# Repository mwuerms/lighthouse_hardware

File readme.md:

# Lighthouse - Hardware

## basic concept

+ lighthouse
+ buoy: hand sender, ble advertising

## lighthouse - electronics

### main board

- RF-MCU: nRF52840: [NINA-B302-00B Module](https://www.mouser.ch/ProductDetail/377-NINA-B302-00B) (ublox)
  - SWDIO connector (50 mil header)
  - RTC (optional): i2c + backup battery CV
  - sound module: [DFPlayer mini](https://wiki.dfrobot.com/DFPlayer_Mini_SKU_DFR0299)
  - display 1: display time
  - display 2: lighting, simulate sunrise
  - Buttons
  - Sensors
    - ambient light sensor (ALS)
      - [VEML7700-TR](https://www.mouser.ch/ProductDetail/78-VEML7700-TR)
      - [TMD37253M](https://www.mouser.ch/ProductDetail/985-TMD37253M) much more than ALS, also proximity and color sensor
      - also maybe [VEML3235](https://www.mouser.ch/ProductDetail/78-VEML3235), [VEML6035](https://www.mouser.ch/ProductDetail/78-VEML6035)
    - rh sensor
      - [SHT40-AD1B-R2](https://www.mouser.ch/ProductDetail/403-SHT40-AD1B-R2)
    - p sensor
      - [DPS368XTSA1](https://www.mouser.ch/ProductDetail/726-DPS368XTSA1)
    - microphone, maybe implement a "do I snore" functionality
      - [CMM-4030DT-26354-TR](https://www.mouser.ch/ProductDetail/490-CMM4030DT26354TR)

### display

- addressable LEDs: [IN-PI22TAT5R5G5B](https://www.mouser.ch/ProductDetail/743-IN-PI22TAT5R5G5B)

### buoy - electronics

- RF-MCU: nRF52811 module [ISP1907-LL-RS](https://www.mouser.ch/ProductDetail/359-ISP1907-LL-RS)
- battery CR2032
- vibration sensor [Adafruit 2384](https://www.mouser.ch/ProductDetail/485-2384)
- button PTS526 [PTS526 SK15 SMTR2 LFS](https://www.mouser.ch/ProductDetail/611-PTS526SK15SMR2L)
- SWDIO connector (50 mil header)

#### schematics

buoy will be soldered together using wire only, no pcb for this.

# links

just a collection of (maybe) useful links

- [markdown cheat sheet](https://www.markdownguide.org/cheat-sheet/)

# ideas

- add many sensors like
  - microphone, analyze snoring
- add memory/flash to log
  - sensor values
  - events
  - errors, ...

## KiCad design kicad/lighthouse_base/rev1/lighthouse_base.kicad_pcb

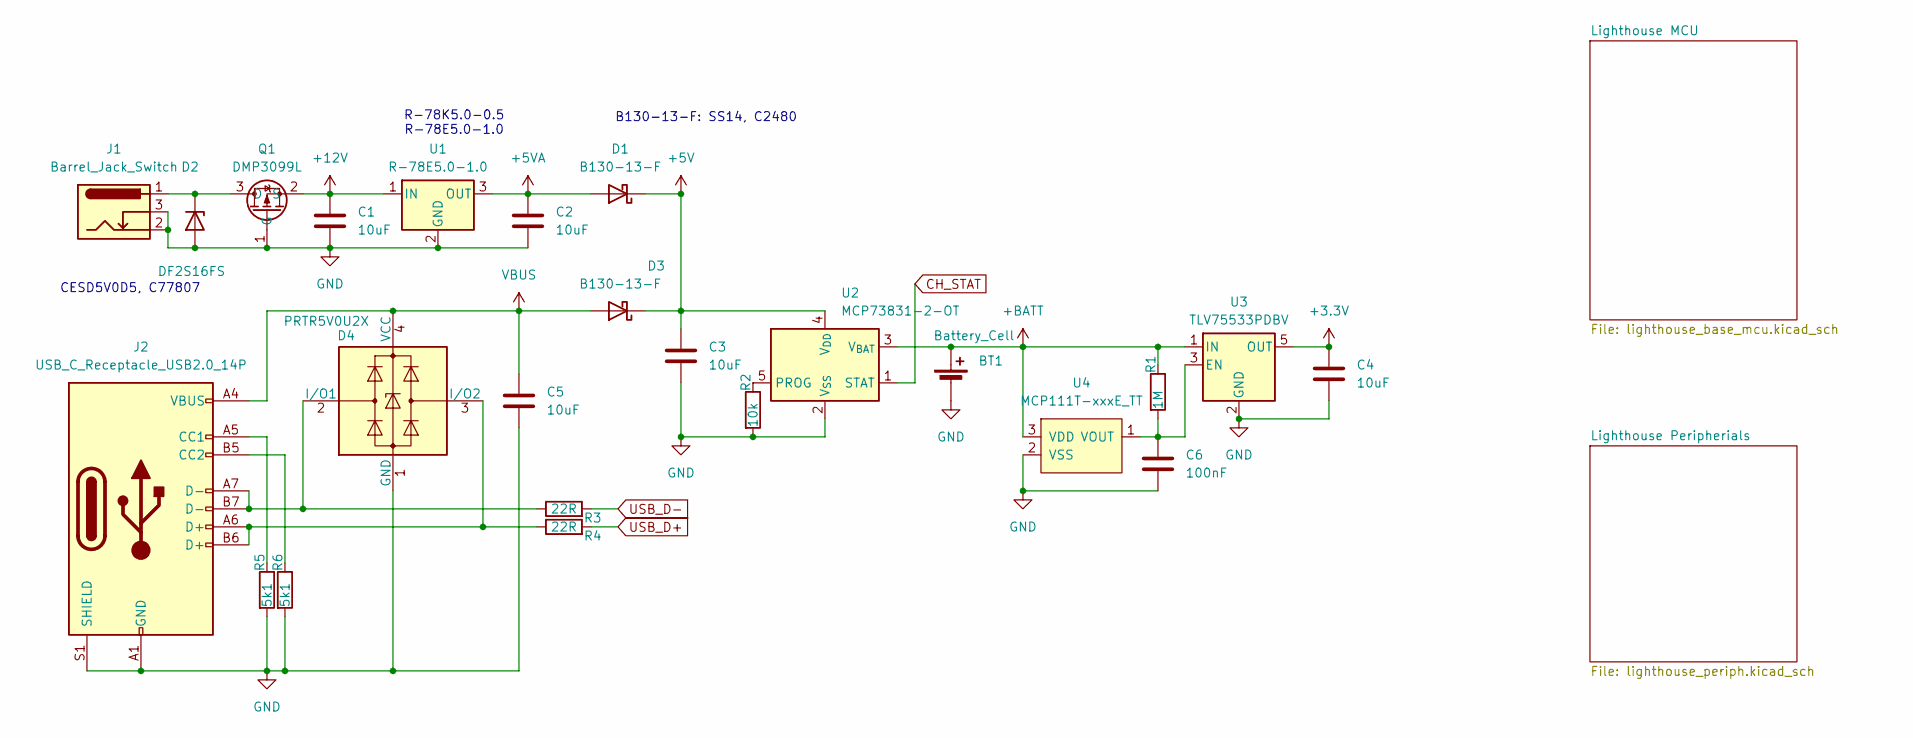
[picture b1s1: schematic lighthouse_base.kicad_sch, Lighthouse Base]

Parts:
BT1: Battery_Cell; PinHeader_1x02_P2.54mm_Vertical
C1, C2, C3, C4, C5: 10uF; C_0805_2012Metric_Pad1.18x1.45mm_HandSolder
C6: 100nF; C_0603_1608Metric_Pad1.08x0.95mm_HandSolder
D1, D3: B130-13-F; D_SMA_Handsoldering
D2: DF2S16FS; D_SOD-523
D4: PRTR5V0U2X; SOT-143
J1: Barrel_Jack_Switch; BarrelJack_CUI_PJ-063AH_Horizontal
J2: USB_C_Receptacle_USB2.0_14P; USB_C_Receptacle_GCT_USB4110
Q1: DMP3099L; SOT-23-3
R1: 1M; R_0603_1608Metric_Pad0.98x0.95mm_HandSolder
R2: 10k; R_0603_1608Metric_Pad0.98x0.95mm_HandSolder
R3, R4: 22R; R_0603_1608Metric_Pad0.98x0.95mm_HandSolder
R5, R6: 5k1; R_0603_1608Metric_Pad0.98x0.95mm_HandSolder
U1: R-78E5.0-1.0; Converter_DCDC_RECOM_R-78E-0.5_THT
U2: MCP73831-2-OT; SOT-23-5
U3: TLV75533PDBV; SOT-23-5
U4: MCP111T-xxxE_TT; SOT-23-3

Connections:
+3.3V: C4.1, U3.5 (OUT); also elsewhere on the board
+5V: C3.1, D1.1 (K), D3.1 (K), U2.4 (V_{DD}); also elsewhere on the board
+5VA: C2.1, D1.2 (A), U1.3 (OUT); also elsewhere on the board
+12V: C1.1, Q1.2 (S), U1.1 (IN); also elsewhere on the board
+BATT: BT1.1 (+), R1.1, U2.3 (V_{BAT}), U3.1 (IN), U4.3 (VDD); also elsewhere on the board
CH_STAT: U2.1 (STAT); also elsewhere on the board
GND: BT1.2 (-), C1.2, C2.2, C3.2, C4.2, C5.2, C6.2, D2.2 (A), D4.1 (GND), J1.2, J1.3, J2.A1 (GND), J2.A12 (GND), J2.B1 (GND), J2.B12 (GND), J2.S1 (SHIELD), Q1.1 (G), R2.2, R5.2, R6.2, U1.2 (GND), U2.2 (V_{SS}), U3.2 (GND), U4.2 (VSS); also elsewhere on the board
unnamed: D2.1 (K), J1.1, Q1.3 (D)
unnamed: D4.2 (I/O1), J2.A7 (D-), J2.B7 (D-), R3.1
unnamed: D4.3 (I/O2), J2.A6 (D+), J2.B6 (D+), R4.1
unnamed: J2.A5 (CC1), R5.1
unnamed: J2.B5 (CC2), R6.1
unnamed: R2.1, U2.5 (PROG)
unnamed: C6.1, R1.2, U3.3 (EN), U4.1 (VOUT)
USB_D+: R4.2; also elsewhere on the board
USB_D-: R3.2; also elsewhere on the board
VBUS: C5.1, D3.2 (A), D4.4 (VCC), J2.A4 (VBUS), J2.A9 (VBUS), J2.B4 (VBUS), J2.B9 (VBUS); also elsewhere on the board

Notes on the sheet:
B130-13-F: SS14, C2480
R-78K5.0-0.5 R-78E5.0-1.0
CESD5V0D5, C77807

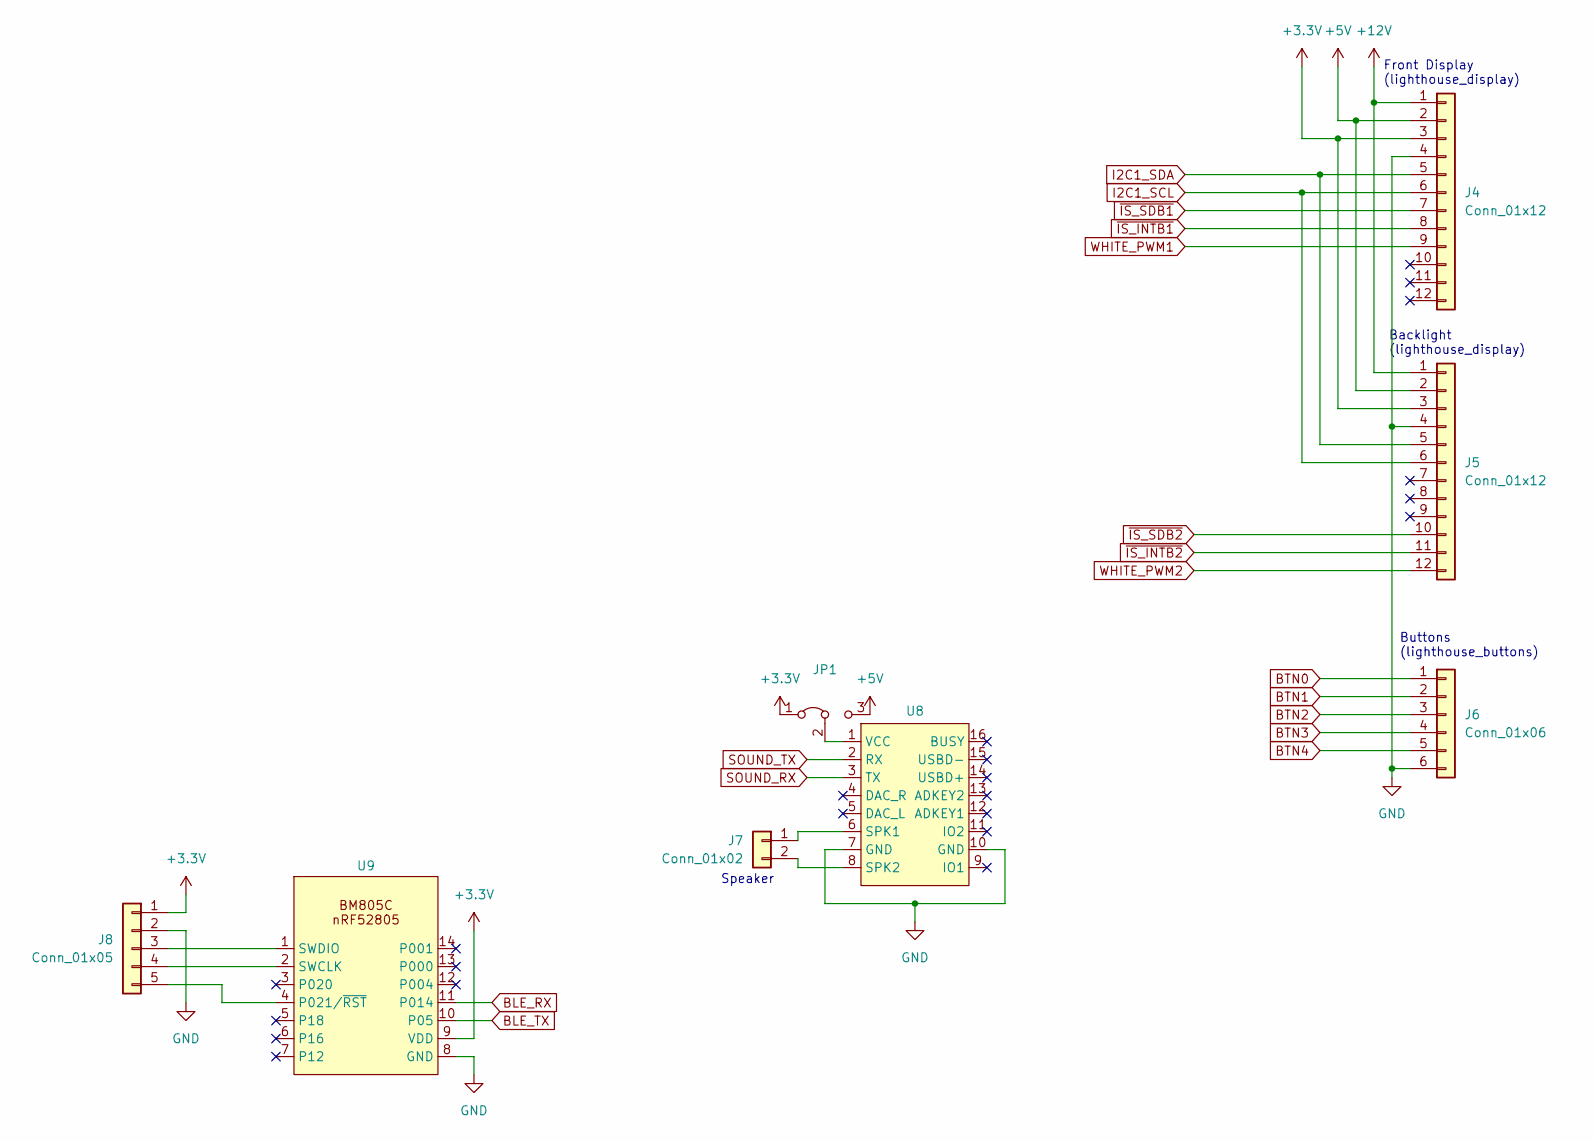
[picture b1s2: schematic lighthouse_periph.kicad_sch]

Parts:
J4, J5: Conn_01x12; Molex_Picoflex_90325-0012_2x06_P1.27mm_Vertical
J6: Conn_01x06; Molex_Picoflex_90325-0006_2x03_P1.27mm_Vertical
J7: Conn_01x02; PinHeader_1x02_P2.54mm_Vertical
J8: Conn_01x05; PinHeader_1x05_P1.27mm_Vertical
JP1: Jumper_3_Bridged12; SolderJumper-3_P1.3mm_Bridged2Bar12_RoundedPad1.0x1.5mm
U8: DFPlayer_Mini-TF-16P
U9: BC805M

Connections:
+3.3V: J4.3, J5.3, J8.1, JP1.1 (A), U9.9 (VDD); also elsewhere on the board
+5V: J4.2, J5.2, JP1.3 (B); also elsewhere on the board
+12V: J4.1, J5.1; also elsewhere on the board
BLE_RX: U9.11 (P014); also elsewhere on the board
BLE_TX: U9.10 (P05); also elsewhere on the board
BTN0: J6.1; also elsewhere on the board
BTN1: J6.2; also elsewhere on the board
BTN2: J6.3; also elsewhere on the board
BTN3: J6.4; also elsewhere on the board
BTN4: J6.5; also elsewhere on the board
GND: J4.4, J5.4, J6.6, J8.2, U8.7 (GND), U8.10 (GND), U9.8 (GND); also elsewhere on the board
I2C1_SCL: J4.6, J5.6; also elsewhere on the board
I2C1_SDA: J4.5, J5.5; also elsewhere on the board
unnamed: J7.1, U8.6 (SPK1)
unnamed: J7.2, U8.8 (SPK2)
unnamed: J8.3, U9.1 (SWDIO)
unnamed: J8.4, U9.2 (SWCLK)
unnamed: J8.5, U9.4 (P021/~RST)
unnamed: JP1.2 (C), U8.1 (VCC)
SOUND_RX: U8.3 (TX); also elsewhere on the board
SOUND_TX: U8.2 (RX); also elsewhere on the board
WHITE_PWM1: J4.9; also elsewhere on the board
WHITE_PWM2: J5.12; also elsewhere on the board
~IS_INTB1: J4.8; also elsewhere on the board
~IS_INTB2: J5.11; also elsewhere on the board
~IS_SDB1: J4.7; also elsewhere on the board
~IS_SDB2: J5.10; also elsewhere on the board

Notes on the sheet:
Front Display (lighthouse_display)
Speaker
Buttons (lighthouse_buttons)
Backlight (lighthouse_display)

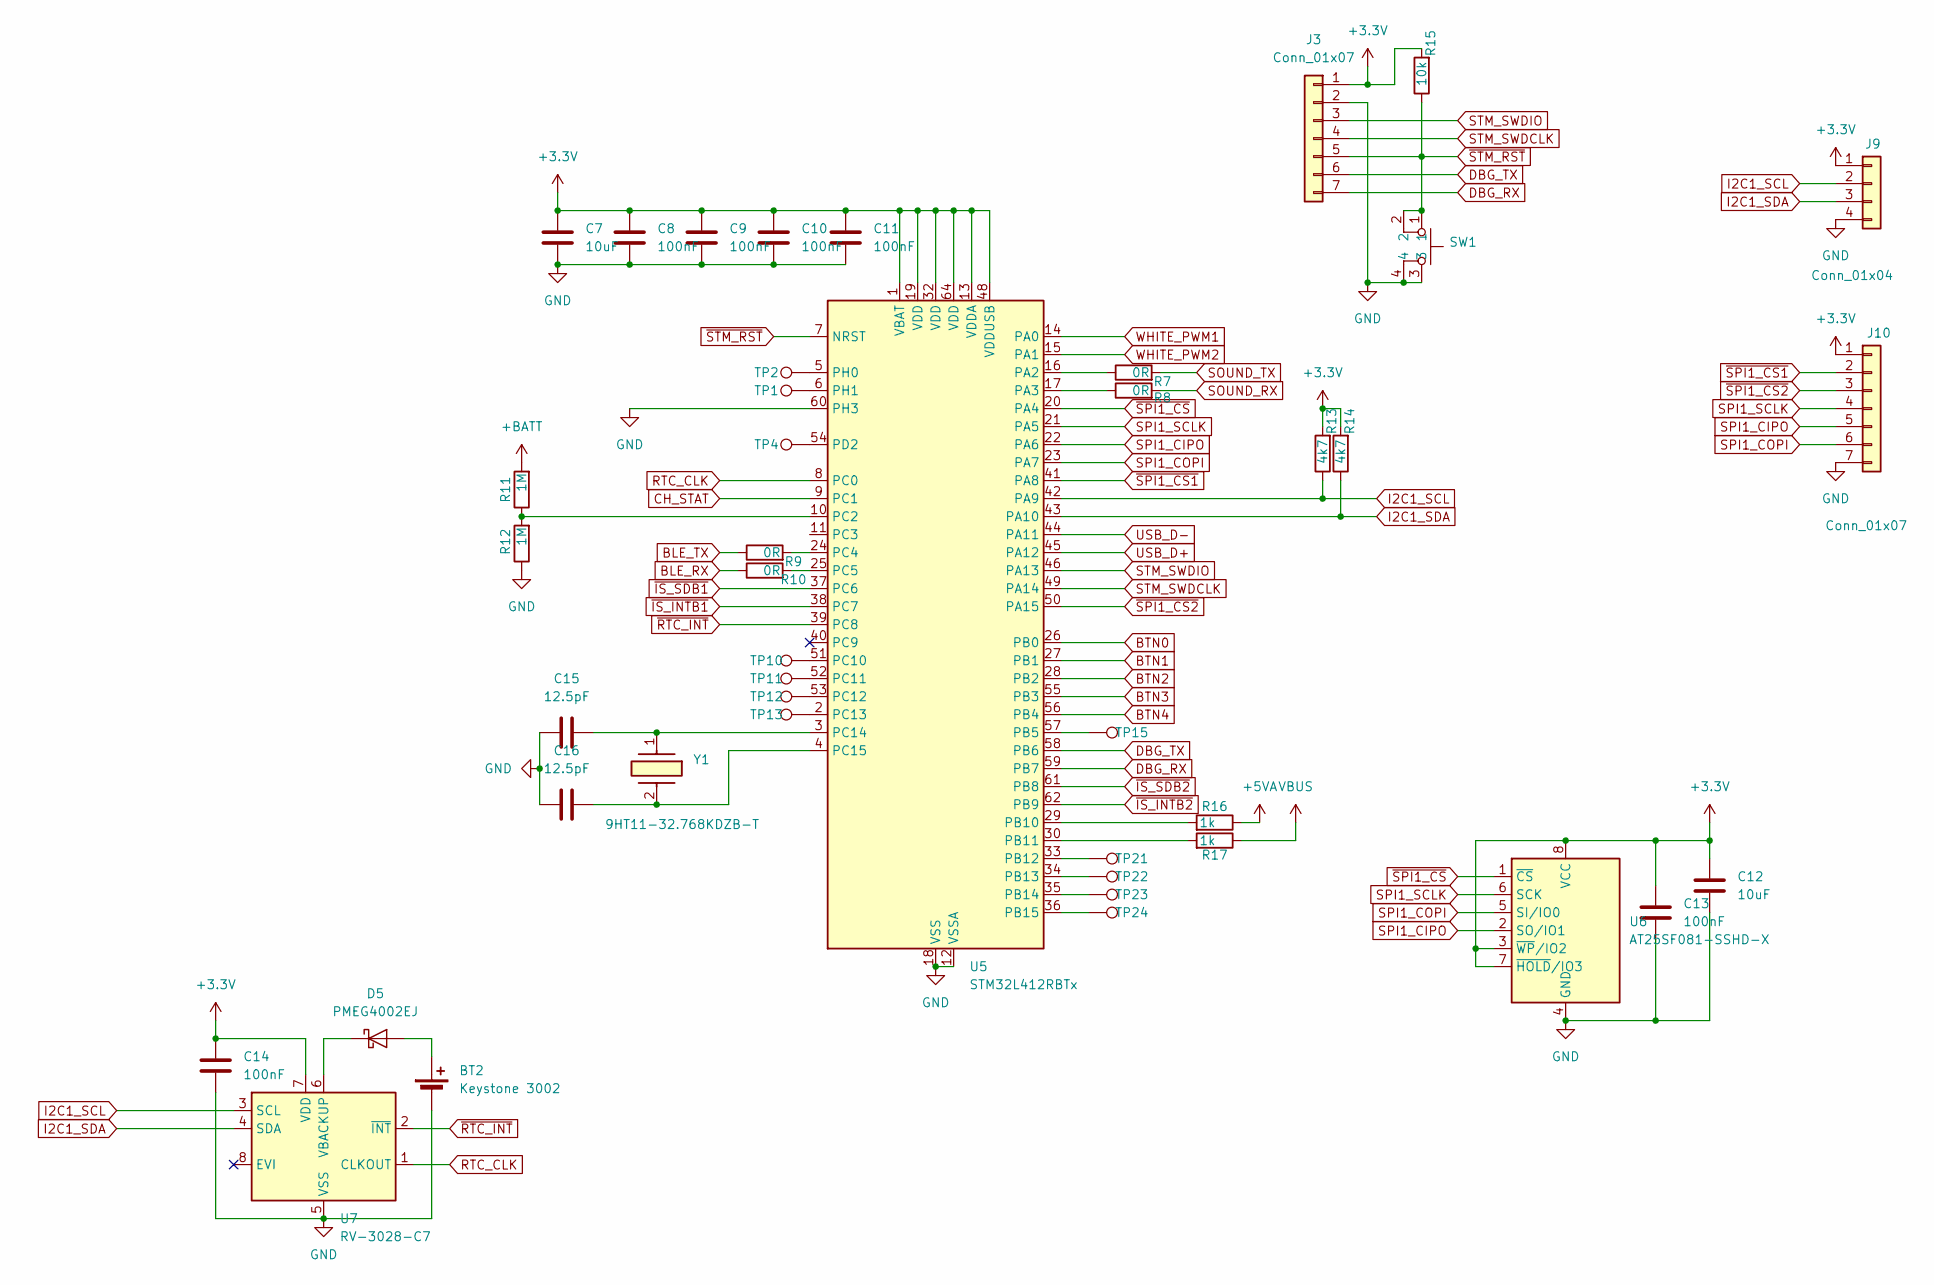
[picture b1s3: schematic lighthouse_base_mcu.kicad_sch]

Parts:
BT2: Keystone 3002; BatteryHolder_Keystone_3002_1x2032
C7, C12: 10uF; C_0805_2012Metric_Pad1.18x1.45mm_HandSolder
C8, C9, C10, C11, C13, C14: 100nF; C_0603_1608Metric_Pad1.08x0.95mm_HandSolder
C15, C16: 12.5pF; C_0603_1608Metric_Pad1.08x0.95mm_HandSolder
D5: PMEG4002EJ; D_SOD-323F
J3: Conn_01x07; PinHeader_1x07_P1.27mm_Vertical
J9: Conn_01x04; PinHeader_1x04_P2.54mm_Vertical
J10: Conn_01x07; PinHeader_1x07_P2.54mm_Vertical
R7, R8, R9, R10: 0R; R_0603_1608Metric_Pad0.98x0.95mm_HandSolder
R11, R12: 1M; R_0603_1608Metric_Pad0.98x0.95mm_HandSolder
R13, R14: 4k7; R_0603_1608Metric_Pad0.98x0.95mm_HandSolder
R15: 10k; R_0603_1608Metric_Pad0.98x0.95mm_HandSolder
R16, R17: 1k; R_0603_1608Metric_Pad0.98x0.95mm_HandSolder
SW1: PTS526
TP1, TP2, TP4, TP10, TP11, TP12, TP13, TP15, TP21, TP22, TP23, TP24: TestPoint; TestPoint_Pad_D1.0mm
U5: STM32L412RBTx; LQFP-64_10x10mm_P0.5mm
U6: AT25SF081-SSHD-X; SOIC-8_3.9x4.9mm_P1.27mm
U7: RV-3028-C7; MicroCrystal_C7_SON-8_1.5x3.2mm_P0.9mm
Y1: 9HT11-32.768KDZB-T; 9HT1132768KDZBT; Manufacturer_Part_Number 9HT11-32.768KDZB-T; Mouser Part Number 717-9HT11-32.76KDZBT

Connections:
+3.3V: C7.1, C8.1, C9.1, C10.1, C11.1, C12.1, C13.1, C14.1, J3.1, J9.1, J10.1, R13.2, R14.2, R15.2, U5.1 (VBAT), U5.13 (VDDA), U5.19 (VDD), U5.32 (VDD), U5.48 (VDDUSB), U5.64 (VDD), U6.3 (~WP/IO2), U6.7 (~HOLD/IO3), U6.8 (VCC), U7.7 (VDD); also elsewhere on the board
+5VA: R16.1; also elsewhere on the board
+BATT: R11.2; also elsewhere on the board
BLE_RX: R10.1; also elsewhere on the board
BLE_TX: R9.1; also elsewhere on the board
BTN0: U5.26 (PB0); also elsewhere on the board
BTN1: U5.27 (PB1); also elsewhere on the board
BTN2: U5.28 (PB2); also elsewhere on the board
BTN3: U5.55 (PB3); also elsewhere on the board
BTN4: U5.56 (PB4); also elsewhere on the board
CH_STAT: U5.9 (PC1); also elsewhere on the board
DBG_RX: J3.7, U5.59 (PB7)
DBG_TX: J3.6, U5.58 (PB6)
GND: BT2.2 (-), C7.2, C8.2, C9.2, C10.2, C11.2, C12.2, C13.2, C14.2, C15.2, C16.2, J3.2, J9.4, J10.7, R12.1, SW1.3, SW1.4, U5.12 (VSSA), U5.18 (VSS), U5.31 (VSS), U5.47 (VSS), U5.60 (PH3), U5.63 (VSS), U6.4 (GND), U7.5 (VSS); also elsewhere on the board
I2C1_SCL: J9.2, R13.1, U5.42 (PA9), U7.3 (SCL); also elsewhere on the board
I2C1_SDA: J9.3, R14.1, U5.43 (PA10), U7.4 (SDA); also elsewhere on the board
unnamed: BT2.1 (+), D5.2 (A)
unnamed: D5.1 (K), U7.6 (VBACKUP)
unnamed: R7.1, U5.16 (PA2)
unnamed: R8.1, U5.17 (PA3)
unnamed: TP15.1, U5.57 (PB5)
unnamed: R16.2, U5.29 (PB10)
unnamed: R17.2, U5.30 (PB11)
unnamed: TP21.1, U5.33 (PB12)
unnamed: TP22.1, U5.34 (PB13)
unnamed: TP23.1, U5.35 (PB14)
unnamed: TP24.1, U5.36 (PB15)
unnamed: R11.1, R12.2, U5.10 (PC2)
unnamed: R9.2, U5.24 (PC4)
unnamed: R10.2, U5.25 (PC5)
unnamed: TP10.1, U5.51 (PC10)
unnamed: TP11.1, U5.52 (PC11)
unnamed: TP12.1, U5.53 (PC12)
unnamed: TP13.1, U5.2 (PC13)
unnamed: C15.1, U5.3 (PC14), Y1.1
unnamed: C16.1, U5.4 (PC15), Y1.2
unnamed: TP4.1, U5.54 (PD2)
unnamed: TP2.1, U5.5 (PH0)
unnamed: TP1.1, U5.6 (PH1)
RTC_CLK: U5.8 (PC0), U7.1 (CLKOUT)
SOUND_RX: R8.2; also elsewhere on the board
SOUND_TX: R7.2; also elsewhere on the board
SPI1_CIPO: J10.5, U5.22 (PA6), U6.2 (SO/IO1)
SPI1_COPI: J10.6, U5.23 (PA7), U6.5 (SI/IO0)
SPI1_SCLK: J10.4, U5.21 (PA5), U6.6 (SCK)
STM_SWDCLK: J3.4, U5.49 (PA14)
STM_SWDIO: J3.3, U5.46 (PA13)
USB_D+: U5.45 (PA12); also elsewhere on the board
USB_D-: U5.44 (PA11); also elsewhere on the board
VBUS: R17.1; also elsewhere on the board
WHITE_PWM1: U5.14 (PA0); also elsewhere on the board
WHITE_PWM2: U5.15 (PA1); also elsewhere on the board
~IS_INTB1: U5.38 (PC7); also elsewhere on the board
~IS_INTB2: U5.62 (PB9); also elsewhere on the board
~IS_SDB1: U5.37 (PC6); also elsewhere on the board
~IS_SDB2: U5.61 (PB8); also elsewhere on the board
~RTC_INT: U5.39 (PC8), U7.2 (~INT)
~SPI1_CS1: J10.2, U5.41 (PA8)
~SPI1_CS2: J10.3, U5.50 (PA15)
~SPI1_CS: U5.20 (PA4), U6.1 (~CS)
~STM_RST: J3.5, R15.1, SW1.1, SW1.2, U5.7 (NRST)

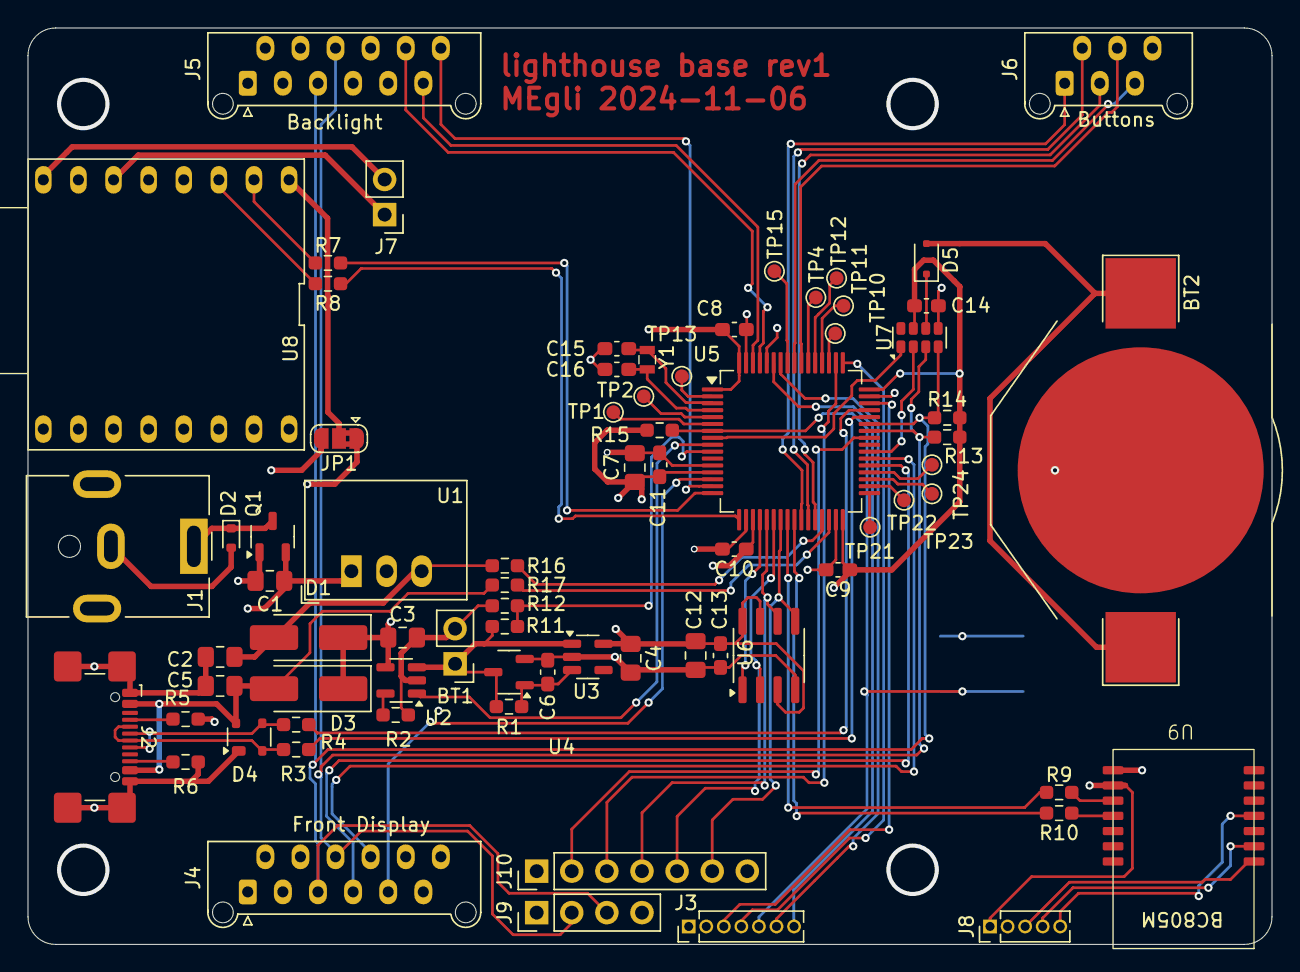
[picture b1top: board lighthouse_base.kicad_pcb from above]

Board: 4 copper layers, 90.0 x 66.3 mm, 75 parts (1 on the bottom side), 76 nets.

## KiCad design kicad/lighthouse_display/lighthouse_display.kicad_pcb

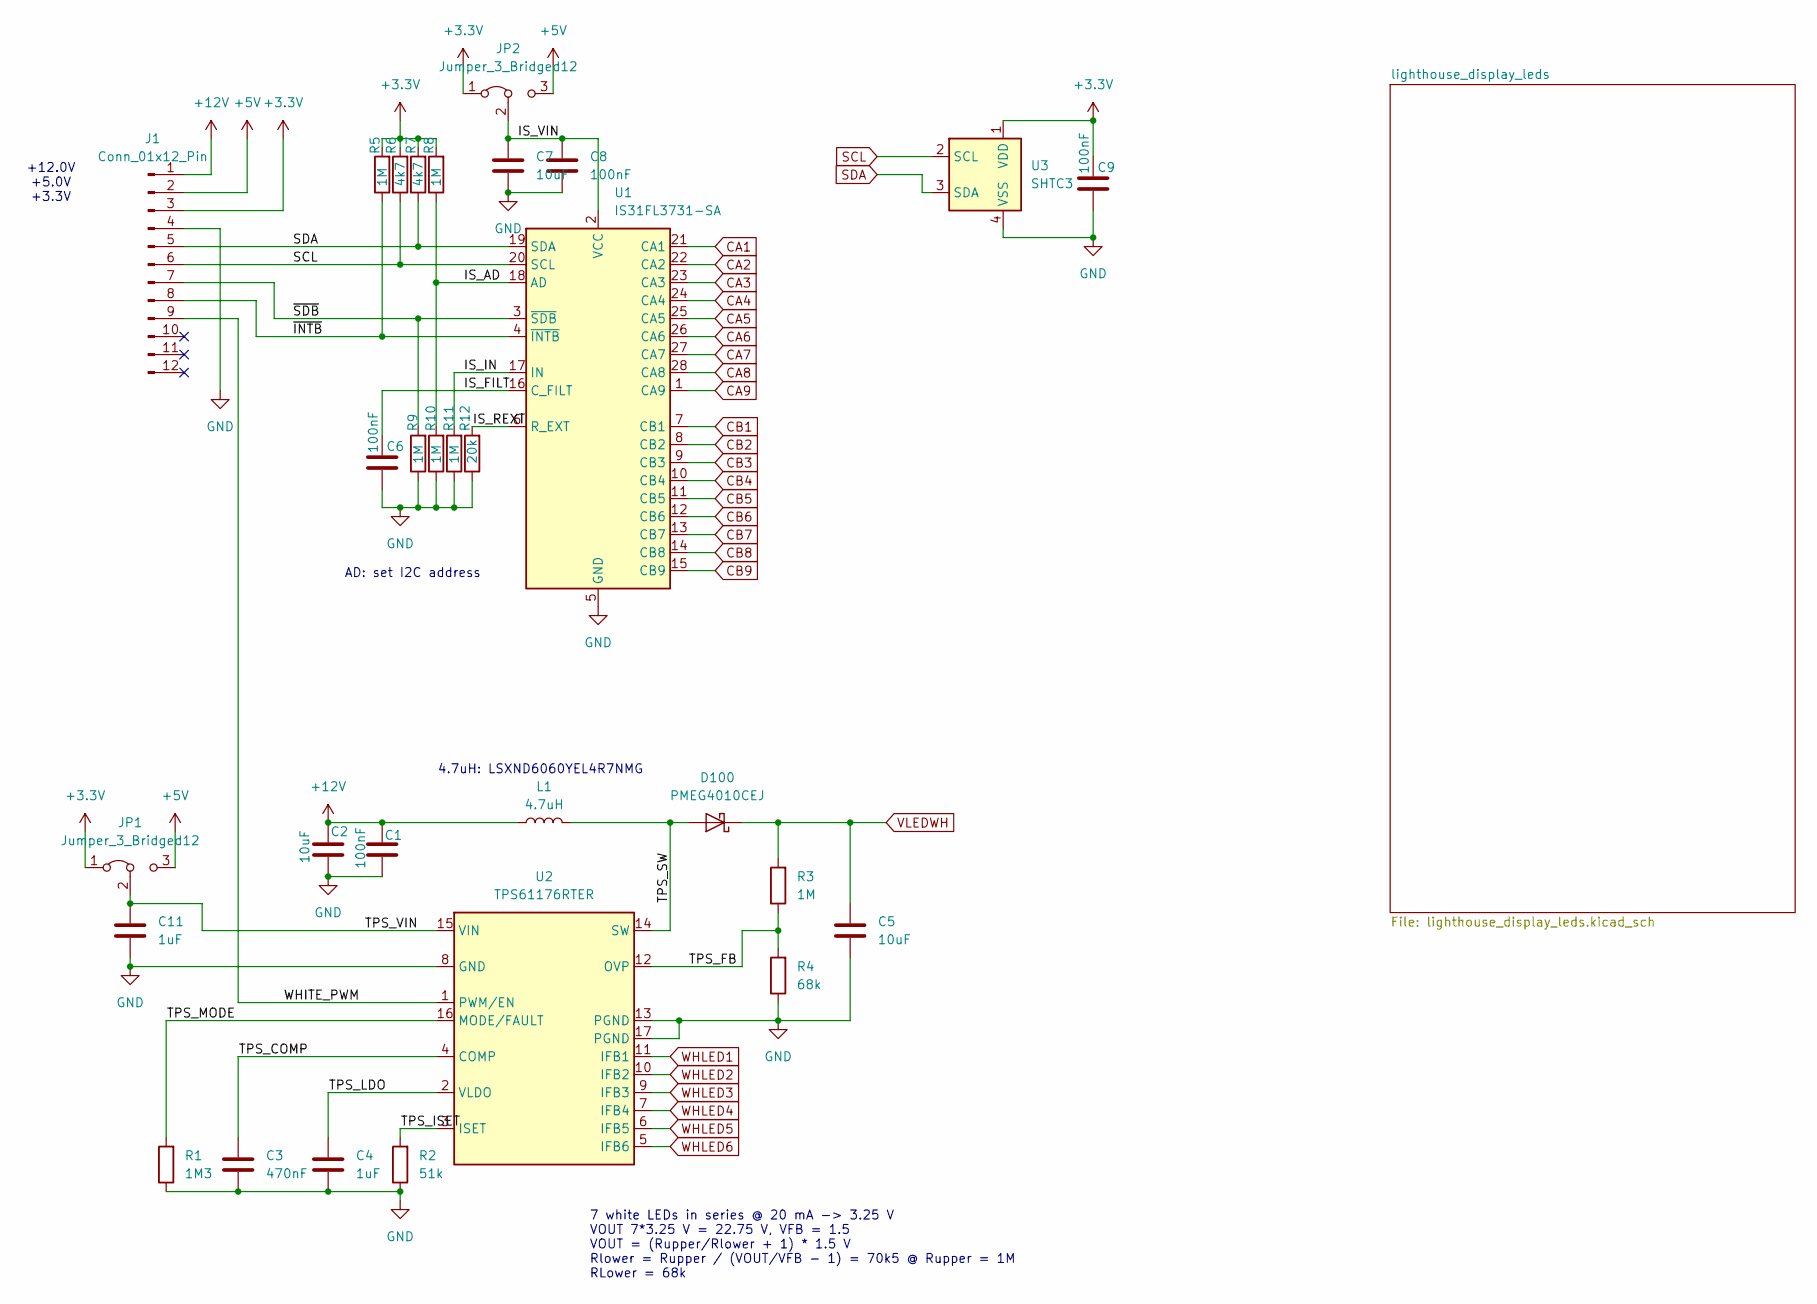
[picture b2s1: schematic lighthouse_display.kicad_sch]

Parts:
C1, C6, C8, C9: 100nF; C_0603_1608Metric_Pad1.08x0.95mm_HandSolder
C2, C5, C7: 10uF; C_0805_2012Metric_Pad1.18x1.45mm_HandSolder
C3: 470nF; C_0603_1608Metric_Pad1.08x0.95mm_HandSolder
C4, C11: 1uF; C_0805_2012Metric_Pad1.18x1.45mm_HandSolder
D100: PMEG4010CEJ; D_SOD-323F
J1: Conn_01x12_Pin; con_1x12_1.27mm_long_pads
JP1, JP2: Jumper_3_Bridged12; SolderJumper-3_P1.3mm_Bridged12_RoundedPad1.0x1.5mm
L1: 4.7uH; L_Taiyo-Yuden_NR-60xx_HandSoldering
R1: 1M3; R_0603_1608Metric_Pad0.98x0.95mm_HandSolder
R2: 51k; R_0603_1608Metric_Pad0.98x0.95mm_HandSolder
R3, R5, R8, R9, R10, R11: 1M; R_0603_1608Metric_Pad0.98x0.95mm_HandSolder
R4: 68k; R_0603_1608Metric_Pad0.98x0.95mm_HandSolder
R6, R7: 4k7; R_0603_1608Metric_Pad0.98x0.95mm_HandSolder
R12: 20k; R_0603_1608Metric_Pad0.98x0.95mm_HandSolder
U1: IS31FL3731-SA; SSOP-28_5.3x10.2mm_P0.65mm
U2: TPS61176RTER; Texas_RTE0016D_WQFN-16-1EP_3x3mm_P0.5mm_EP0.8x0.8mm
U3: SHTC3; Sensirion_DFN-4-1EP_2x2mm_P1mm_EP0.7x1.6mm

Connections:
+3.3V: C9.1, J1.3, JP1.1 (A), JP2.1 (A), R5.2, R6.2, R7.2, R8.2, U3.1 (VDD)
+5V: J1.2, JP1.3 (B), JP2.3 (B)
+12V: C1.1, C2.1, J1.1, L1.1
/IS_AD: R8.1, R10.2, U1.18 (AD)
/IS_FILT: C6.1, U1.16 (C_FILT)
/IS_IN: R11.2, U1.17 (IN)
/IS_REXT: R12.2, U1.6 (R_EXT)
/IS_VIN: C7.1, C8.1, JP2.2 (C), U1.2 (VCC)
/TPS_COMP: C3.1, U2.4 (COMP)
/TPS_FB: R3.1, R4.2, U2.12 (OVP)
/TPS_ISET: R2.2, U2.3 (ISET)
/TPS_LDO: C4.1, U2.2 (VLDO)
/TPS_MODE: R1.2, U2.16 (MODE/FAULT)
/TPS_SW: D100.2 (A), L1.2, U2.14 (SW)
/TPS_VIN: C11.1, JP1.2 (C), U2.15 (VIN)
/WHITE_PWM: J1.9, U2.1 (PWM/EN)
/~INTB: J1.8, R5.1, U1.4 (~INTB)
/~SDB: J1.7, R9.2, U1.3 (~SDB)
CA1: U1.21 (CA1); also elsewhere on the board
CA2: U1.22 (CA2); also elsewhere on the board
CA3: U1.23 (CA3); also elsewhere on the board
CA4: U1.24 (CA4); also elsewhere on the board
CA5: U1.25 (CA5); also elsewhere on the board
CA6: U1.26 (CA6); also elsewhere on the board
CA7: U1.27 (CA7); also elsewhere on the board
CA8: U1.28 (CA8); also elsewhere on the board
CA9: U1.1 (CA9); also elsewhere on the board
CB1: U1.7 (CB1); also elsewhere on the board
CB2: U1.8 (CB2); also elsewhere on the board
CB3: U1.9 (CB3); also elsewhere on the board
CB4: U1.10 (CB4); also elsewhere on the board
CB5: U1.11 (CB5); also elsewhere on the board
CB6: U1.12 (CB6); also elsewhere on the board
CB7: U1.13 (CB7); also elsewhere on the board
CB8: U1.14 (CB8); also elsewhere on the board
CB9: U1.15 (CB9); also elsewhere on the board
GND: C1.2, C2.2, C3.2, C4.2, C5.2, C6.2, C7.2, C8.2, C9.2, C11.2, J1.4, R1.1, R2.1, R4.1, R9.1, R10.1, R11.1, R12.1, U1.5 (GND), U2.8 (GND), U2.13 (PGND), U2.17 (PGND), U3.4 (VSS)
SCL: J1.6, R6.1, U1.20 (SCL), U3.2 (SCL)
SDA: J1.5, R7.1, U1.19 (SDA), U3.3 (SDA)
VLEDWH: C5.1, D100.1 (K), R3.2; also elsewhere on the board
WHLED1: U2.11 (IFB1); also elsewhere on the board
WHLED2: U2.10 (IFB2); also elsewhere on the board
WHLED3: U2.9 (IFB3); also elsewhere on the board
WHLED4: U2.7 (IFB4); also elsewhere on the board
WHLED5: U2.6 (IFB5); also elsewhere on the board
WHLED6: U2.5 (IFB6); also elsewhere on the board

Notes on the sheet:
AD: set I2C address
4.7uH: LSXND6060YEL4R7NMG
7 white LEDs in series @ 20 mA -> 3.25 V VOUT 7*3.25 V = 22.75 V, VFB = 1.5 VOUT = (Rupper/Rlower + 1) * 1.5 V Rlower = Rupper / (VOUT/VFB - 1) = 70k5 @ Rupper = 1M RLower = 68k
+12.0V +5.0V +3.3V

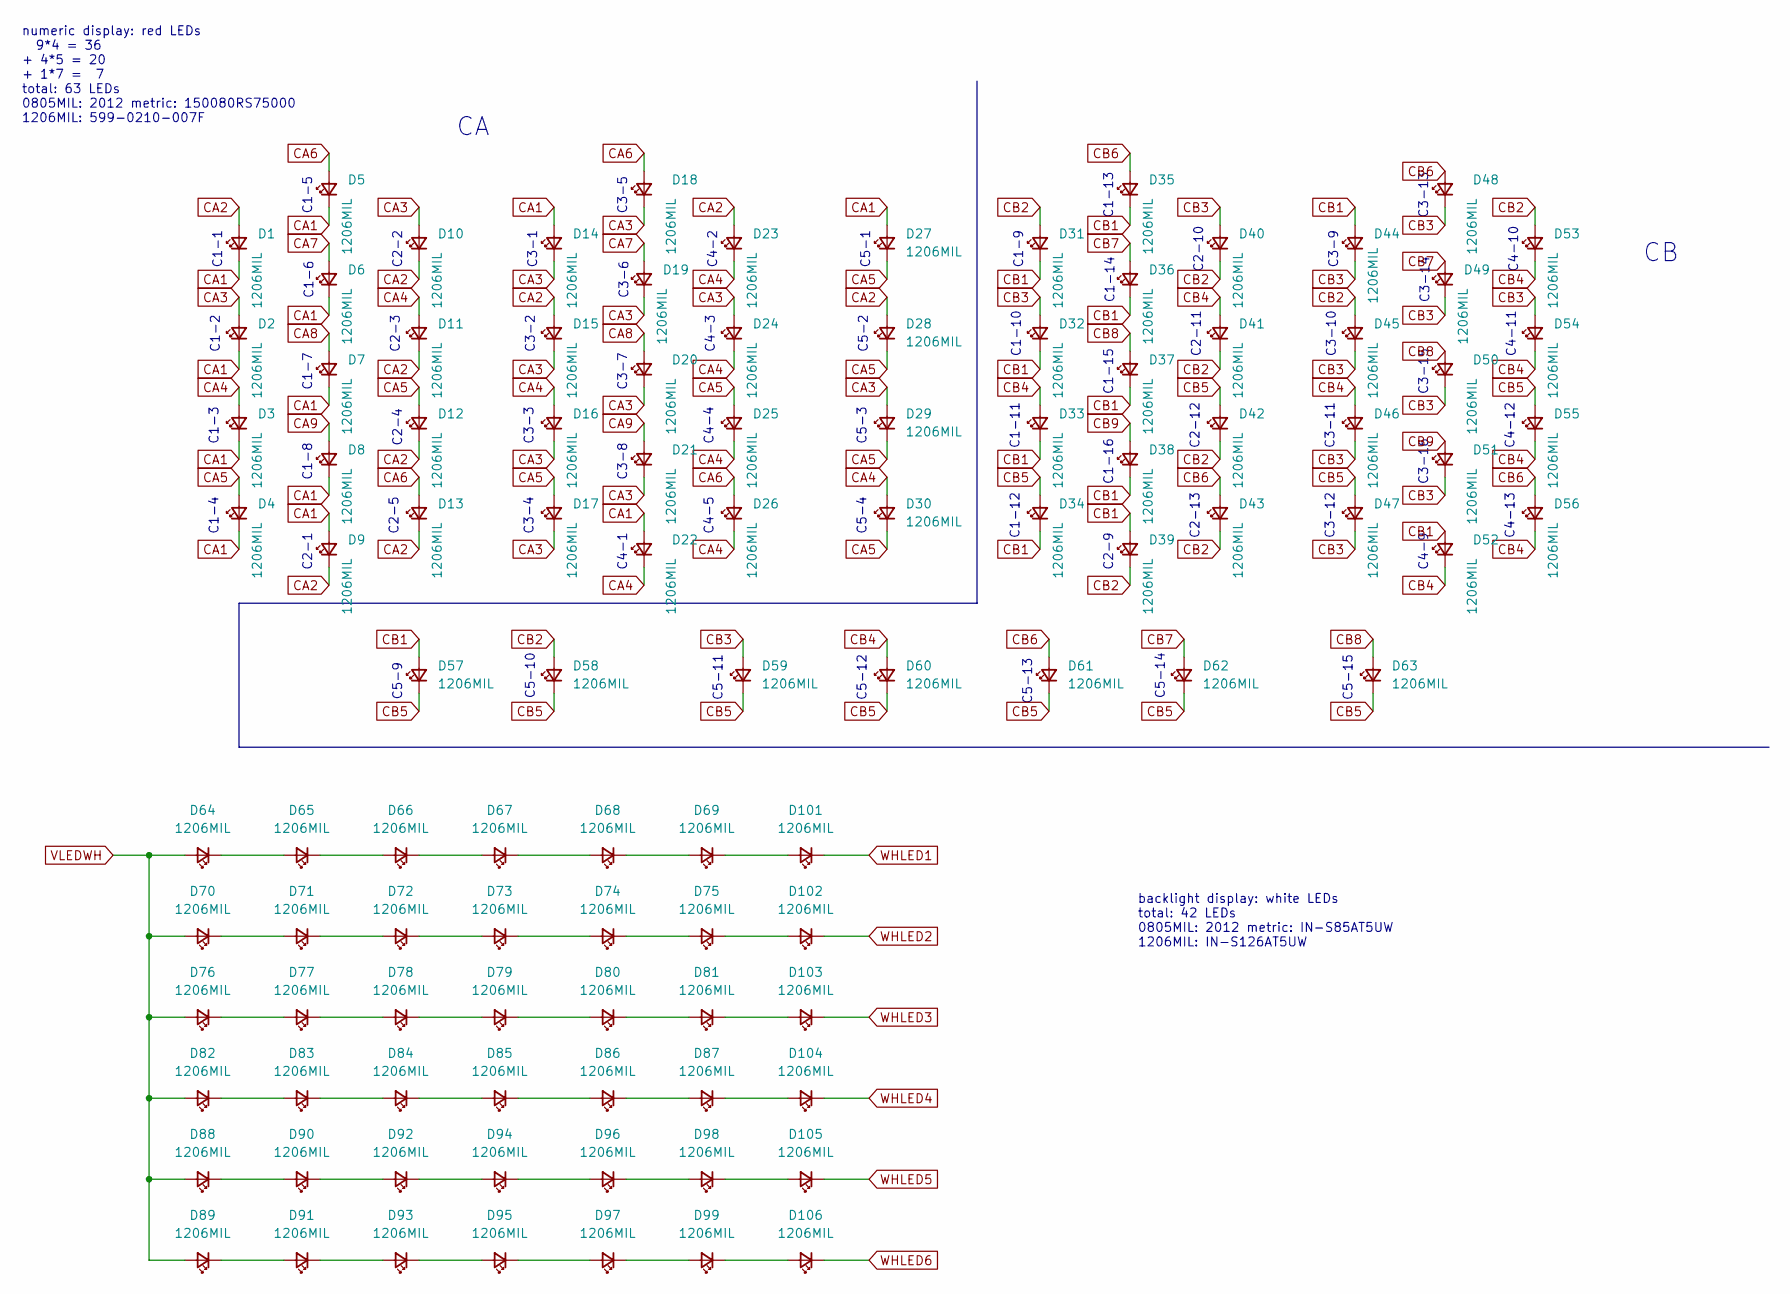
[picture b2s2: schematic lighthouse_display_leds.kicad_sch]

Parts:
D1, D2, D3, D4, D5, D6, D7, D8, D9, D10, D11, D12, D13, D14, D15, D16, D17, D18, D19, D20, D21, D22, D23, D24, D25, D26, D27, D28, D29, D30, D31, D32, D33, D34, D35, D36, D37, D38, D39, D40, D41, D42, D43, D44, D45, D46, D47, D48, D49, D50, D51, D52, D53, D54, D55, D56, D57, D58, D59, D60, D61, D62, D63, D64, D65, D66, D67, D68, D69, D70, D71, D72, D73, D74, D75, D76, D77, D78, D79, D80, D81, D82, D83, D84, D85, D86, D87, D88, D89, D90, D91, D92, D93, D94, D95, D96, D97, D98, D99, D101, D102, D103, D104, D105, D106: 1206MIL; LED_1206_3216Metric_Pad1.42x1.75mm_HandSolder

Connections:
CA1: D1.1 (K), D2.1 (K), D3.1 (K), D4.1 (K), D5.1 (K), D6.1 (K), D7.1 (K), D8.1 (K), D9.2 (A), D14.2 (A), D22.2 (A), D27.2 (A); also elsewhere on the board
CA2: D1.2 (A), D9.1 (K), D10.1 (K), D11.1 (K), D12.1 (K), D13.1 (K), D15.2 (A), D23.2 (A), D28.2 (A); also elsewhere on the board
CA3: D2.2 (A), D10.2 (A), D14.1 (K), D15.1 (K), D16.1 (K), D17.1 (K), D18.1 (K), D19.1 (K), D20.1 (K), D21.1 (K), D24.2 (A), D29.2 (A); also elsewhere on the board
CA4: D3.2 (A), D11.2 (A), D16.2 (A), D22.1 (K), D23.1 (K), D24.1 (K), D25.1 (K), D26.1 (K), D30.2 (A); also elsewhere on the board
CA5: D4.2 (A), D12.2 (A), D17.2 (A), D25.2 (A), D27.1 (K), D28.1 (K), D29.1 (K), D30.1 (K); also elsewhere on the board
CA6: D5.2 (A), D13.2 (A), D18.2 (A), D26.2 (A); also elsewhere on the board
CA7: D6.2 (A), D19.2 (A); also elsewhere on the board
CA8: D7.2 (A), D20.2 (A); also elsewhere on the board
CA9: D8.2 (A), D21.2 (A); also elsewhere on the board
CB1: D31.1 (K), D32.1 (K), D33.1 (K), D34.1 (K), D35.1 (K), D36.1 (K), D37.1 (K), D38.1 (K), D39.2 (A), D44.2 (A), D52.2 (A), D57.2 (A); also elsewhere on the board
CB2: D31.2 (A), D39.1 (K), D40.1 (K), D41.1 (K), D42.1 (K), D43.1 (K), D45.2 (A), D53.2 (A), D58.2 (A); also elsewhere on the board
CB3: D32.2 (A), D40.2 (A), D44.1 (K), D45.1 (K), D46.1 (K), D47.1 (K), D48.1 (K), D49.1 (K), D50.1 (K), D51.1 (K), D54.2 (A), D59.2 (A); also elsewhere on the board
CB4: D33.2 (A), D41.2 (A), D46.2 (A), D52.1 (K), D53.1 (K), D54.1 (K), D55.1 (K), D56.1 (K), D60.2 (A); also elsewhere on the board
CB5: D34.2 (A), D42.2 (A), D47.2 (A), D55.2 (A), D57.1 (K), D58.1 (K), D59.1 (K), D60.1 (K), D61.1 (K), D62.1 (K), D63.1 (K); also elsewhere on the board
CB6: D35.2 (A), D43.2 (A), D48.2 (A), D56.2 (A), D61.2 (A); also elsewhere on the board
CB7: D36.2 (A), D49.2 (A), D62.2 (A); also elsewhere on the board
CB8: D37.2 (A), D50.2 (A), D63.2 (A); also elsewhere on the board
CB9: D38.2 (A), D51.2 (A); also elsewhere on the board
unnamed: D64.1 (K), D65.2 (A)
unnamed: D65.1 (K), D66.2 (A)
unnamed: D66.1 (K), D67.2 (A)
unnamed: D67.1 (K), D68.2 (A)
unnamed: D68.1 (K), D69.2 (A)
unnamed: D70.1 (K), D71.2 (A)
unnamed: D71.1 (K), D72.2 (A)
unnamed: D72.1 (K), D73.2 (A)
unnamed: D73.1 (K), D74.2 (A)
unnamed: D74.1 (K), D75.2 (A)
unnamed: D76.1 (K), D77.2 (A)
unnamed: D77.1 (K), D78.2 (A)
unnamed: D78.1 (K), D79.2 (A)
unnamed: D79.1 (K), D80.2 (A)
unnamed: D80.1 (K), D81.2 (A)
unnamed: D82.1 (K), D83.2 (A)
unnamed: D83.1 (K), D84.2 (A)
unnamed: D84.1 (K), D85.2 (A)
unnamed: D85.1 (K), D86.2 (A)
unnamed: D86.1 (K), D87.2 (A)
unnamed: D88.1 (K), D90.2 (A)
unnamed: D89.1 (K), D91.2 (A)
unnamed: D90.1 (K), D92.2 (A)
unnamed: D91.1 (K), D93.2 (A)
unnamed: D92.1 (K), D94.2 (A)
unnamed: D93.1 (K), D95.2 (A)
unnamed: D94.1 (K), D96.2 (A)
unnamed: D95.1 (K), D97.2 (A)
unnamed: D96.1 (K), D98.2 (A)
unnamed: D97.1 (K), D99.2 (A)
unnamed: D69.1 (K), D101.2 (A)
unnamed: D75.1 (K), D102.2 (A)
unnamed: D81.1 (K), D103.2 (A)
unnamed: D87.1 (K), D104.2 (A)
unnamed: D98.1 (K), D105.2 (A)
unnamed: D99.1 (K), D106.2 (A)
VLEDWH: D64.2 (A), D70.2 (A), D76.2 (A), D82.2 (A), D88.2 (A), D89.2 (A); also elsewhere on the board
WHLED1: D101.1 (K); also elsewhere on the board
WHLED2: D102.1 (K); also elsewhere on the board
WHLED3: D103.1 (K); also elsewhere on the board
WHLED4: D104.1 (K); also elsewhere on the board
WHLED5: D105.1 (K); also elsewhere on the board
WHLED6: D106.1 (K); also elsewhere on the board

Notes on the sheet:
C3-13
C2-1
C5-11
C3-14
C3-5
C3-6
C4-13
C1-15
C2-10
C3-16
C4-5
C4-11
C1-13
C1-8
C2-2
C4-4
C3-12
C1-14
C1-10
backlight display: white LEDs total: 42 LEDs 0805MIL: 2012 metric: IN-S85AT5UW 1206MIL: IN-S126AT5UW
C4-10
C3-3
C2-11
C5-13
C4-1
C1-1
C4-3
C2-4
numeric display: red LEDs 9*4 = 36 + 4*5 = 20 + 1*7 = 7 total: 63 LEDs 0805MIL: 2012 metric: 150080RS75000 1206MIL: 599-0210-007F
C1-7
C3-15
C1-11
C1-4
C3-2
C3-8
C1-9
C5-2
C3-11
C4-12
C4-9

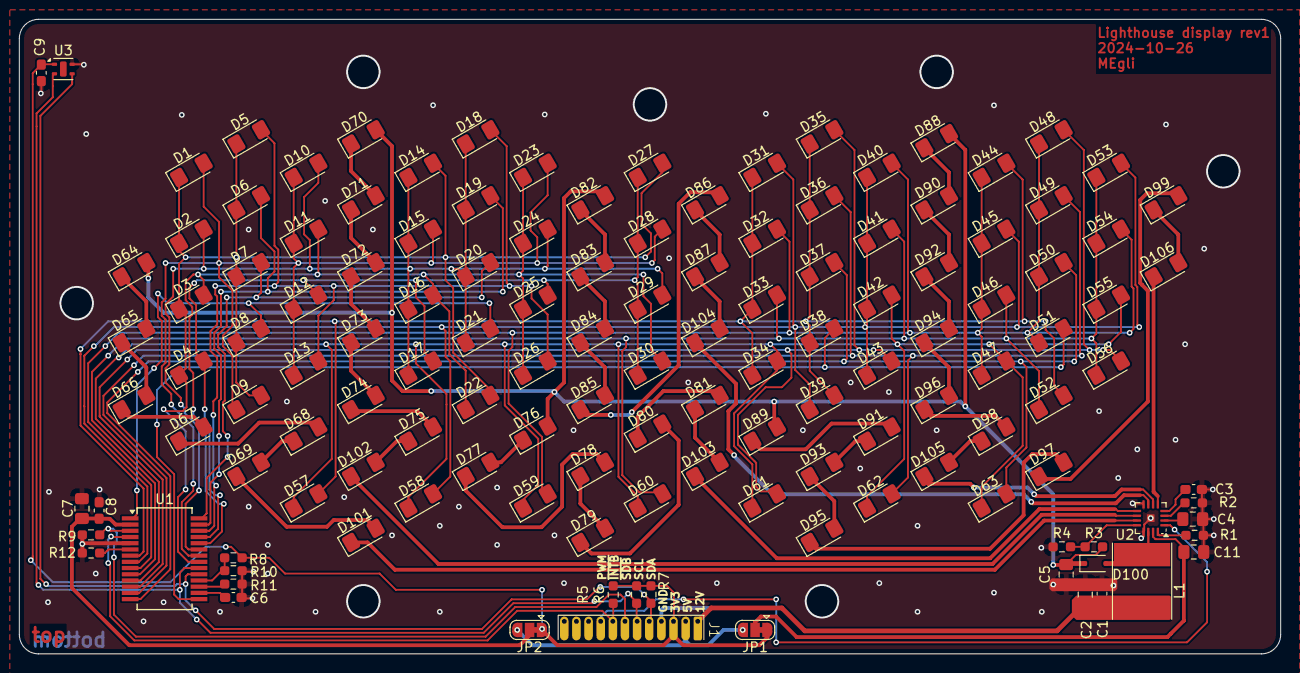
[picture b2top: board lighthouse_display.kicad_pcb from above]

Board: 2 copper layers, 132.0 x 66.4 mm, 135 parts (0 on the bottom side), 82 nets.
